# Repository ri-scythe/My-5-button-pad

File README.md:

# wildpad
A custom 5 button macropad built for the Hack Club Hackpad project. It features 2 layers for shortcuts and gifs, 5 keycaps, OLED screen and a rotary encoder. 

# CAD

# PCB
Created in KiCad.

PCB 

Schematic

# Firmware
This macropad uses [QMK](https://qmk.fm/) firmware.

- The rotary encoder changes volume.
- The 4 keys on the first layer are used to open apps and turn on bluetooth, the same 4 keys display different GIFS on OLED, and 1 of the keys is for changing the layer.

# BOM

- 5x Cherry MX Switches
- 5x DSA Keycaps
- 4x M3x5x4 Heatset inserts
- 4x M3x16mm Screws
- 1x EC11 Rotary Encoder
- 1x 0.91" OLED Display
- 1x Seeed Studio XIAO RP2040
- 5x SK6812 MINI LEDs
- 6x Through-hole 1N4148 Diodes
- 1x Case(2 separate parts)
- 1x Soldering Iron

# Fun fact

i actually had a black bunny

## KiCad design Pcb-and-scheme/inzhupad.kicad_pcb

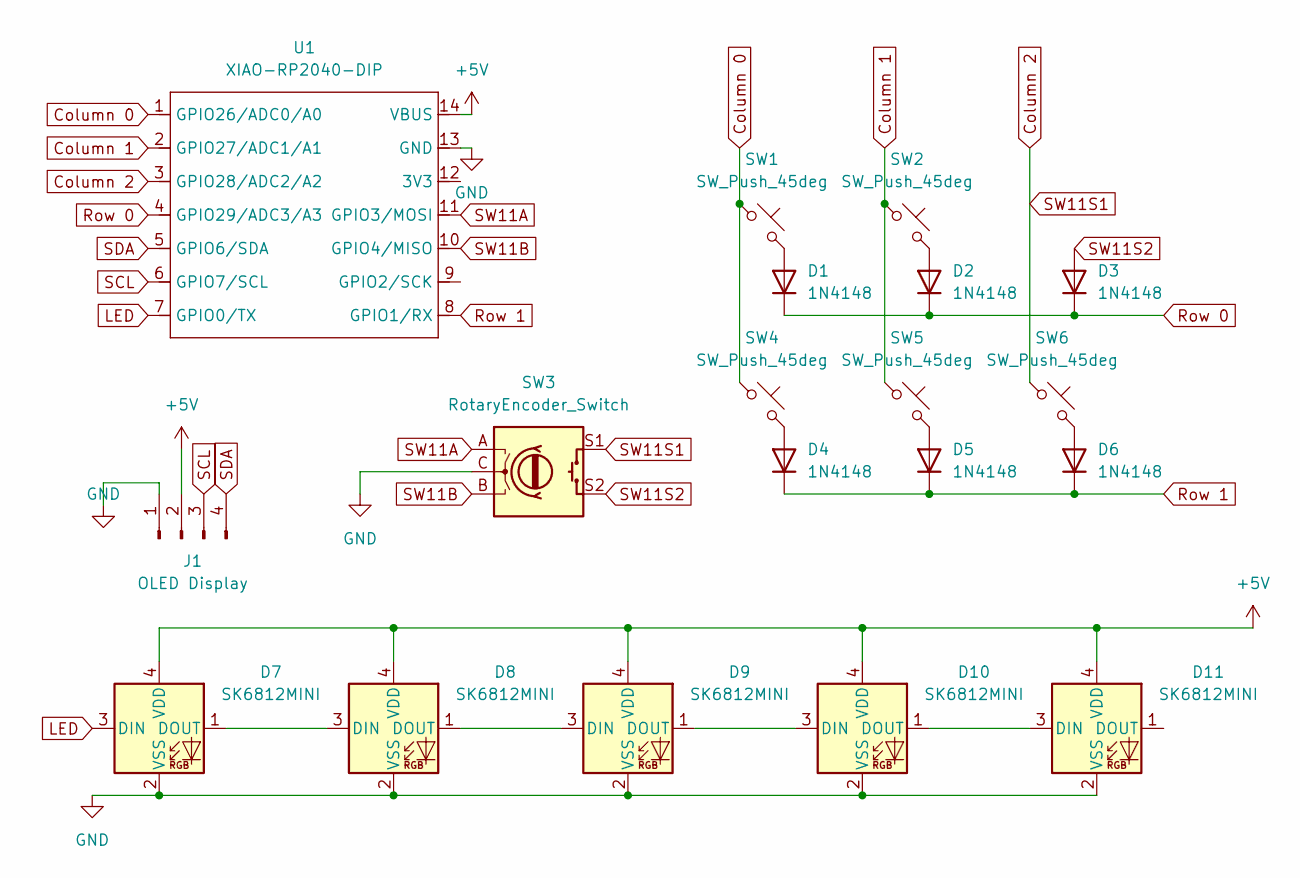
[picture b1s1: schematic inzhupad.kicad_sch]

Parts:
D1, D2, D3, D4, D5, D6: 1N4148; D_DO-35_SOD27_P7.62mm_Horizontal
D7, D8, D9, D10, D11: SK6812MINI; LED_SK6812MINI_PLCC4_3.5x3.5mm_P1.75mm
J1: OLED Display; FanPinHeader_1x04_P2.54mm_Vertical
SW1, SW2, SW4, SW5, SW6: SW_Push_45deg; SW_Cherry_MX_1.00u_PCB
SW3: RotaryEncoder_Switch; RotaryEncoder_Alps_EC11E-Switch_Vertical_H20mm
U1: XIAO-RP2040-DIP

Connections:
+5V: D7.4 (VDD), D8.4 (VDD), D9.4 (VDD), D10.4 (VDD), D11.4 (VDD), J1.2, U1.14 (VBUS)
Column 0: SW1.1, SW4.1, U1.1 (GPIO26/ADC0/A0)
Column 1: SW2.1, SW5.1, U1.2 (GPIO27/ADC1/A1)
Column 2: SW3.S1, SW6.1, U1.3 (GPIO28/ADC2/A2)
GND: D7.2 (VSS), D8.2 (VSS), D9.2 (VSS), D10.2 (VSS), D11.2 (VSS), J1.1, SW3.C, U1.13 (GND)
LED: D7.3 (DIN), U1.7 (GPIO0/TX)
unnamed: D1.2 (A), SW1.2
unnamed: D2.2 (A), SW2.2
unnamed: D4.2 (A), SW4.2
unnamed: D5.2 (A), SW5.2
unnamed: D6.2 (A), SW6.2
unnamed: D7.1 (DOUT), D8.3 (DIN)
unnamed: D8.1 (DOUT), D9.3 (DIN)
unnamed: D9.1 (DOUT), D10.3 (DIN)
unnamed: D10.1 (DOUT), D11.3 (DIN)
Row 0: D1.1 (K), D2.1 (K), D3.1 (K), U1.4 (GPIO29/ADC3/A3)
Row 1: D4.1 (K), D5.1 (K), D6.1 (K), U1.8 (GPIO1/RX)
SCL: J1.3, U1.6 (GPIO7/SCL)
SDA: J1.4, U1.5 (GPIO6/SDA)
SW11A: SW3.A, U1.11 (GPIO3/MOSI)
SW11B: SW3.B, U1.10 (GPIO4/MISO)
SW11S2: D3.2 (A), SW3.S2

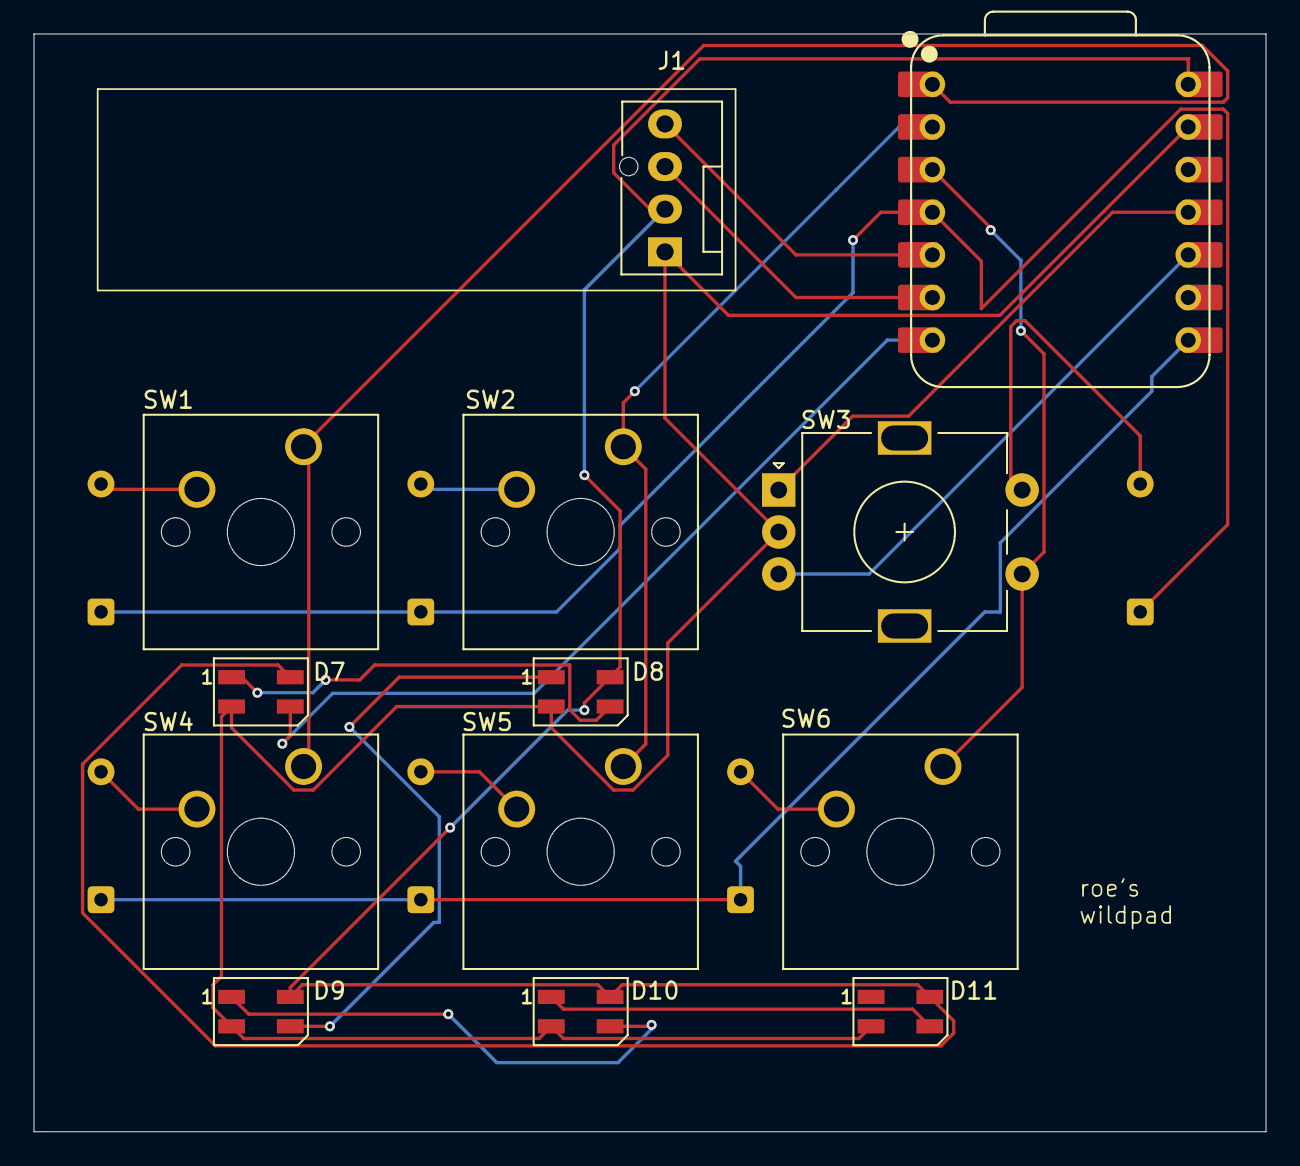
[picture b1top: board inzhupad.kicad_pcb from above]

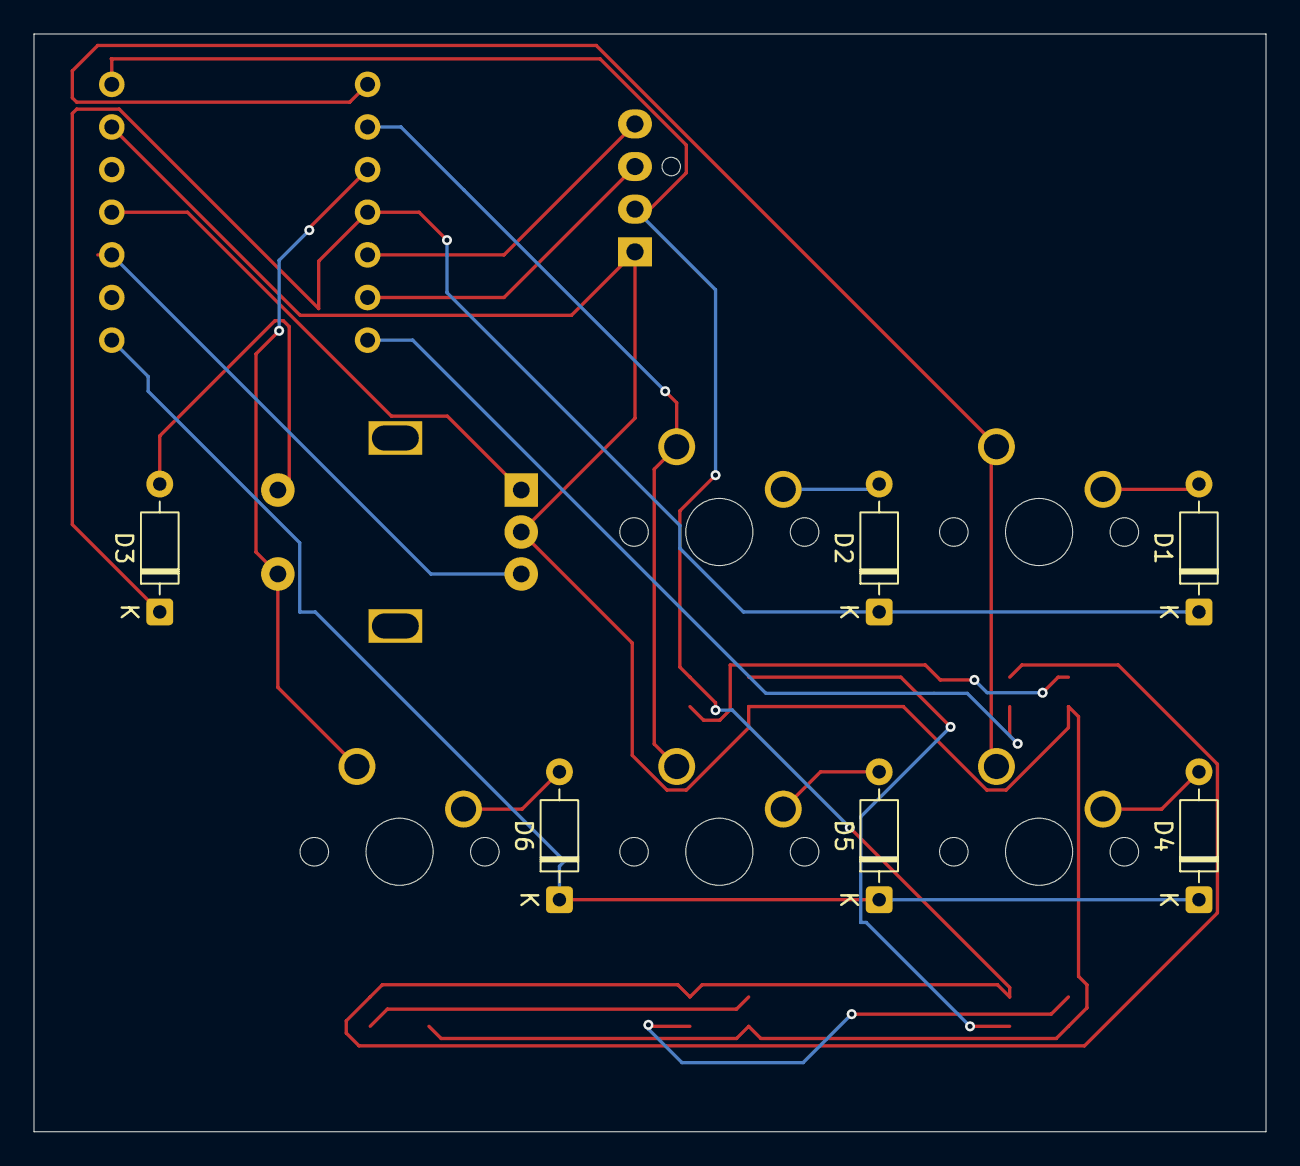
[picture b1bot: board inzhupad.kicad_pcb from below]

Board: 2 copper layers, 73.4 x 65.4 mm, 19 parts (6 on the bottom side), 22 nets.

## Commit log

2026-02-21 Create PCB and SCHEMATIC
2026-02-21 Create Pcb
2026-02-21 Scheme
2026-02-28 /CAD
2026-02-28 Create w
2026-02-28 Create a
2026-02-28 Create s
2026-03-01 Remove 6x 1N4148 Diodes from README
    Removed mention of 6x 1N4148 Diodes from the README.
